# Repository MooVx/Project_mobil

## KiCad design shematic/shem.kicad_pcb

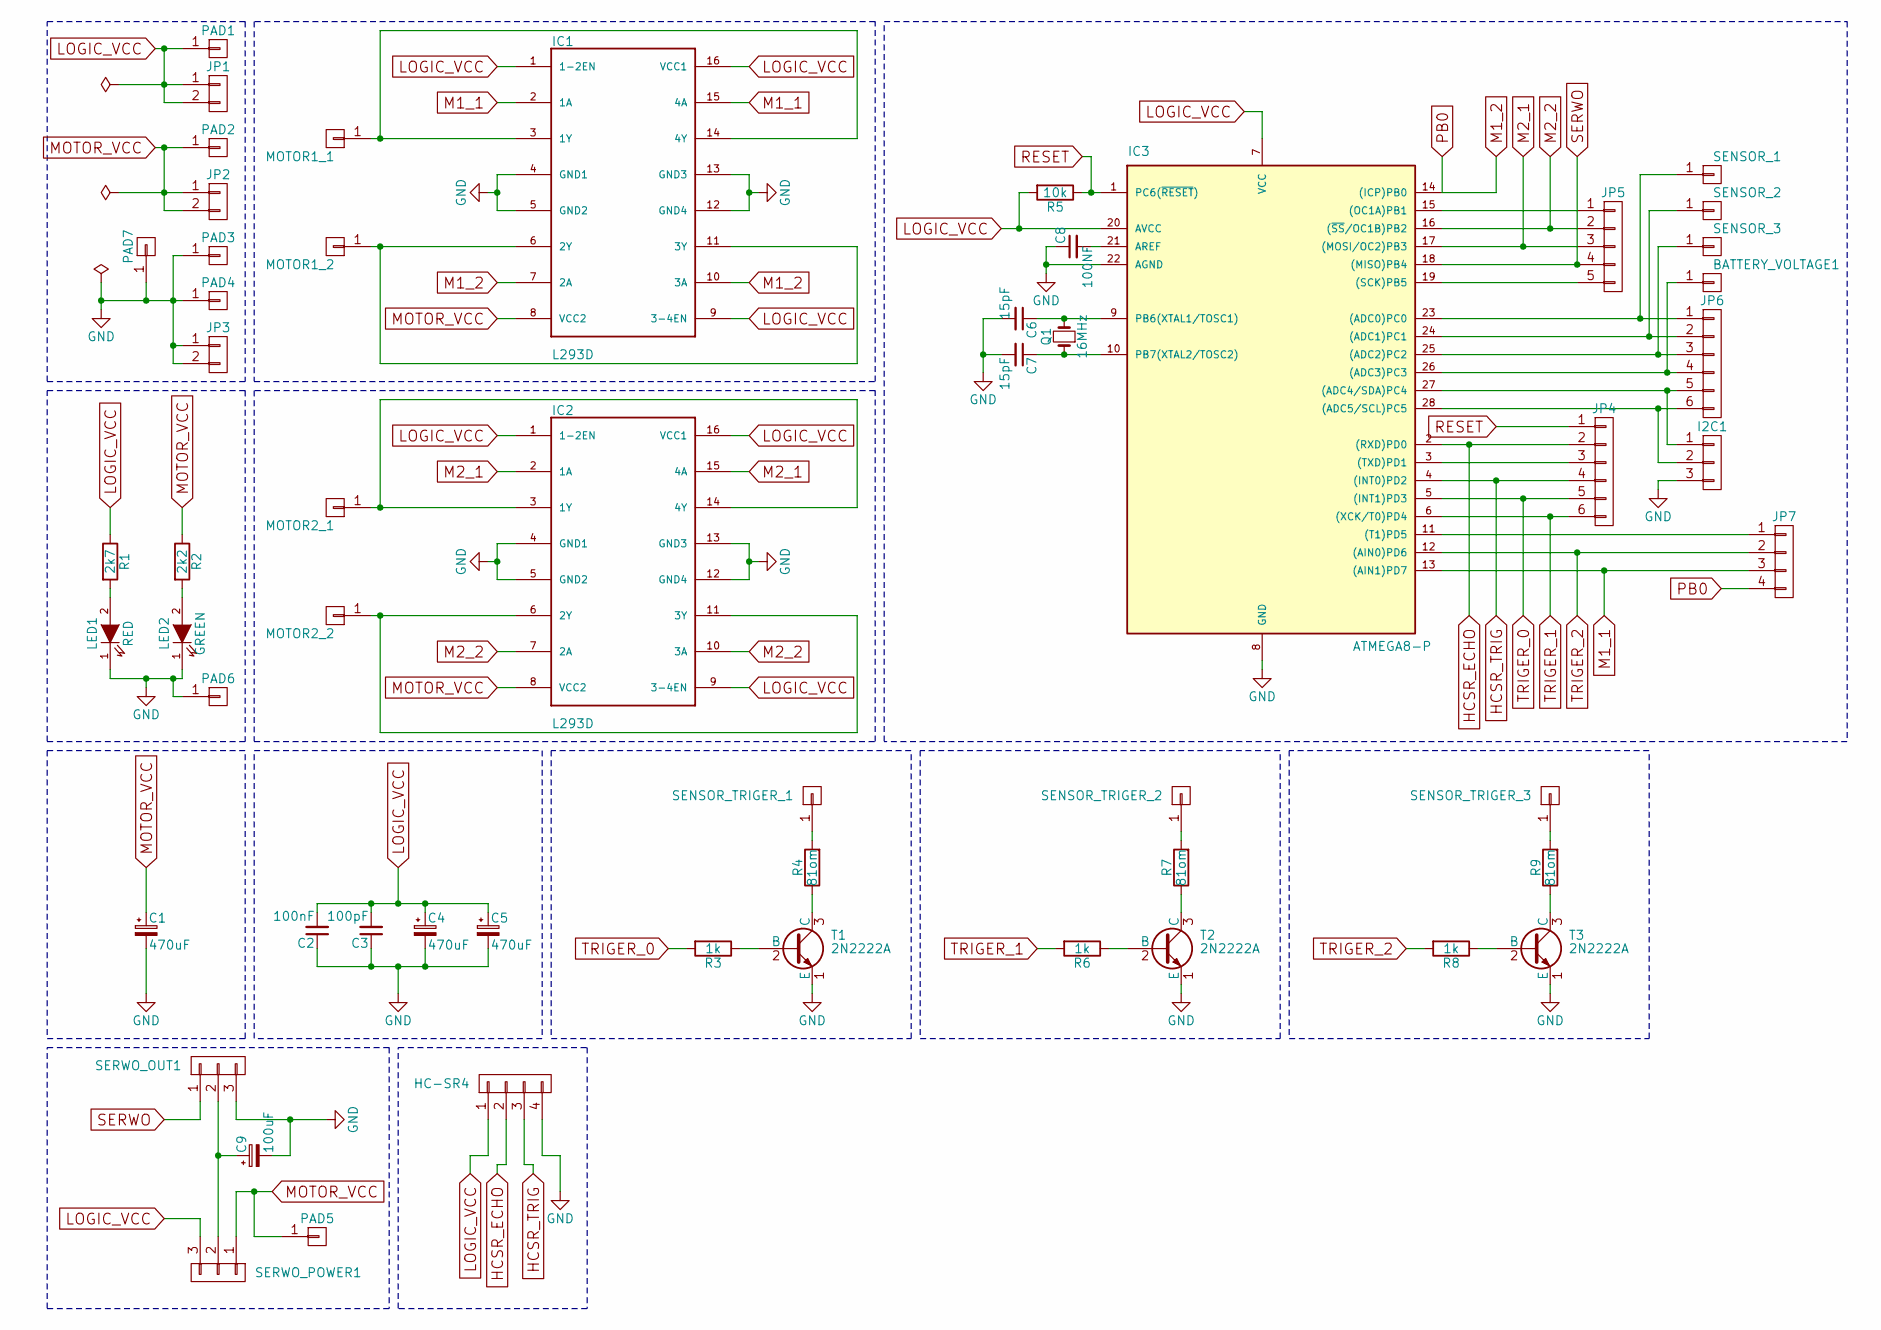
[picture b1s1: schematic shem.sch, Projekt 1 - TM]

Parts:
BATTERY_VOLTAGE1: CONN_01X01; SolderWirePad_single_1-5mmDrill
C1, C4, C5: 470uF; CP_Radial_D8.0mm_P3.80mm
C2: 100nF; C_Rect_L7.0mm_W2.0mm_P5.00mm
C3: 100pF; C_Disc_D3.8mm_W2.6mm_P2.50mm
C6, C7: 15pF; C_Disc_D3.4mm_W2.1mm_P2.50mm
C8: 100NF; C_Disc_D5.0mm_W2.5mm_P2.50mm
C9: 100uF; CP_Radial_D5.0mm_P2.00mm
HC-SR4: CONN_01X04; Pin_Header_Straight_1x04_Pitch2.54mm
I2C1: CONN_01X03; Pin_Header_Straight_1x03_Pitch2.54mm
IC1, IC2: L293D; DIP-16_W7.62mm_LongPads
IC3: ATMEGA8-P; DIP-28_W7.62mm_LongPads
JP1, JP2, JP3: CONN_01X02; Pin_Header_Straight_1x02_Pitch2.54mm
JP4, JP6: CONN_01X06; Pin_Header_Straight_1x06_Pitch2.54mm
JP5: CONN_01X05; Pin_Header_Straight_1x05_Pitch2.54mm
JP7: CONN_01X04; Pin_Header_Straight_1x04_Pitch2.54mm
LED1: RED; LED_D5.0mm
LED2: GREEN; LED_D5.0mm
MOTOR1_1, MOTOR1_2, MOTOR2_1, MOTOR2_2: CONN_01X01; SolderWirePad_single_1-5mmDrill
PAD1, PAD2, PAD3, PAD4, PAD5, PAD6, PAD7: CONN_01X01; SolderWirePad_single_1-2mmDrill
Q1: 16MHz; Crystal_HC49-U_Vertical
R1: 2k7; R_Axial_DIN0207_L6.3mm_D2.5mm_P10.16mm_Horizontal
R2: 2k2; R_Axial_DIN0207_L6.3mm_D2.5mm_P10.16mm_Horizontal
R3, R6, R8: 1k; R_Axial_DIN0207_L6.3mm_D2.5mm_P10.16mm_Horizontal
R4, R7, R9: 81om; R_Axial_DIN0207_L6.3mm_D2.5mm_P10.16mm_Horizontal
R5: 10k; R_Axial_DIN0207_L6.3mm_D2.5mm_P10.16mm_Horizontal
SENSOR_1, SENSOR_2, SENSOR_3: CONN_01X01; SolderWirePad_single_1-5mmDrill
SENSOR_TRIGER_1, SENSOR_TRIGER_2, SENSOR_TRIGER_3: CONN_01X01; SolderWirePad_single_1-5mmDrill
SERWO_OUT1: CONN_01X03; Pin_Header_Straight_1x03_Pitch2.54mm
SERWO_POWER1: CONN_01X03; Pin_Header_Straight_1x03_Pitch2.54mm
T1, T2, T3: 2N2222A; TO-92_Molded_Narrow

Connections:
GND: C1.2, C2.1, C3.1, C4.2, C5.2, C6.2, C7.2, C8.1, C9.2, HC-SR4.4, I2C1.3, IC1.4 (GND1), IC1.5 (GND2), IC1.12 (GND4), IC1.13 (GND3), IC2.4 (GND1), IC2.5 (GND2), IC2.12 (GND4), IC2.13 (GND3), IC3.8 (GND), IC3.22 (AGND), JP3.1, JP3.2, LED1.1 (K), LED2.1 (K), PAD3.1, PAD4.1, PAD6.1, PAD7.1, SERWO_OUT1.3, T1.1 (E), T2.1 (E), T3.1 (E); also elsewhere on the board
HCSR_ECHO: HC-SR4.2, IC3.2 ((RXD)PD0), JP4.2
HCSR_TRIG: HC-SR4.3, IC3.4 ((INT0)PD2), JP4.4
LOGIC_VCC: C2.2, C3.2, C4.1, C5.1, HC-SR4.1, IC1.1 (1-2EN), IC1.9 (3-4EN), IC1.16 (VCC1), IC2.1 (1-2EN), IC2.9 (3-4EN), IC2.16 (VCC1), IC3.7 (VCC), IC3.20 (AVCC), JP1.1, JP1.2, PAD1.1, R1.1, R5.2, SERWO_POWER1.3; also elsewhere on the board
M1_1: IC1.2 (1A), IC1.15 (4A), IC3.13 ((AIN1)PD7), JP7.3
M1_2: IC1.7 (2A), IC1.10 (3A), IC3.14 ((ICP)PB0), JP7.4
M2_1: IC2.2 (1A), IC2.15 (4A), IC3.17 ((MOSI/OC2)PB3), JP5.3
M2_2: IC2.7 (2A), IC2.10 (3A), IC3.16 ((~SS~/OC1B)PB2), JP5.2
MOTOR_VCC: C1.1, IC1.8 (VCC2), IC2.8 (VCC2), JP2.1, JP2.2, PAD2.1, PAD5.1, R2.1, SERWO_POWER1.1; also elsewhere on the board
unnamed 9: BATTERY_VOLTAGE1.1, IC3.26 ((ADC3)PC3), JP6.4; also elsewhere on the board
unnamed: C6.1, IC3.9 (PB6(XTAL1/TOSC1)), Q1.2
unnamed: C7.1, IC3.10 (PB7(XTAL2/TOSC2)), Q1.1
unnamed: C8.2, IC3.21 (AREF)
unnamed 13: C9.1, SERWO_OUT1.2, SERWO_POWER1.2; also elsewhere on the board
unnamed 14: I2C1.1, IC3.27 ((ADC4/SDA)PC4), JP6.5; also elsewhere on the board
unnamed 15: I2C1.2, IC3.28 ((ADC5/SCL)PC5), JP6.6; also elsewhere on the board
unnamed: IC1.6 (2Y), IC1.11 (3Y), MOTOR1_2.1
unnamed: IC1.3 (1Y), IC1.14 (4Y), MOTOR1_1.1
unnamed: IC2.6 (2Y), IC2.11 (3Y), MOTOR2_2.1
unnamed: IC2.3 (1Y), IC2.14 (4Y), MOTOR2_1.1
unnamed: IC3.3 ((TXD)PD1), JP4.3
unnamed: IC3.11 ((T1)PD5), JP7.1
unnamed: IC3.15 ((OC1A)PB1), JP5.1
unnamed: IC3.19 ((SCK)PB5), JP5.5
unnamed: IC3.23 ((ADC0)PC0), JP6.1, SENSOR_1.1
unnamed: IC3.24 ((ADC1)PC1), JP6.2, SENSOR_2.1
unnamed: IC3.25 ((ADC2)PC2), JP6.3, SENSOR_3.1
unnamed: LED1.2 (A), R1.2
unnamed: LED2.2 (A), R2.2
unnamed: R3.1, T1.2 (B)
unnamed: R4.1, T1.3 (C)
unnamed: R4.2, SENSOR_TRIGER_1.1
unnamed: R6.1, T2.2 (B)
unnamed: R7.1, T2.3 (C)
unnamed: R7.2, SENSOR_TRIGER_2.1
unnamed: R8.1, T3.2 (B)
unnamed: R9.1, T3.3 (C)
unnamed: R9.2, SENSOR_TRIGER_3.1
RESET: IC3.1 (PC6(~RESET~)), JP4.1, R5.1
SERWO: IC3.18 ((MISO)PB4), JP5.4, SERWO_OUT1.1; also elsewhere on the board
TRIGER_0: IC3.5 ((INT1)PD3), JP4.5, R3.2
TRIGER_1: IC3.6 ((XCK/T0)PD4), JP4.6, R6.2
TRIGER_2: IC3.12 ((AIN0)PD6), JP7.2, R8.2

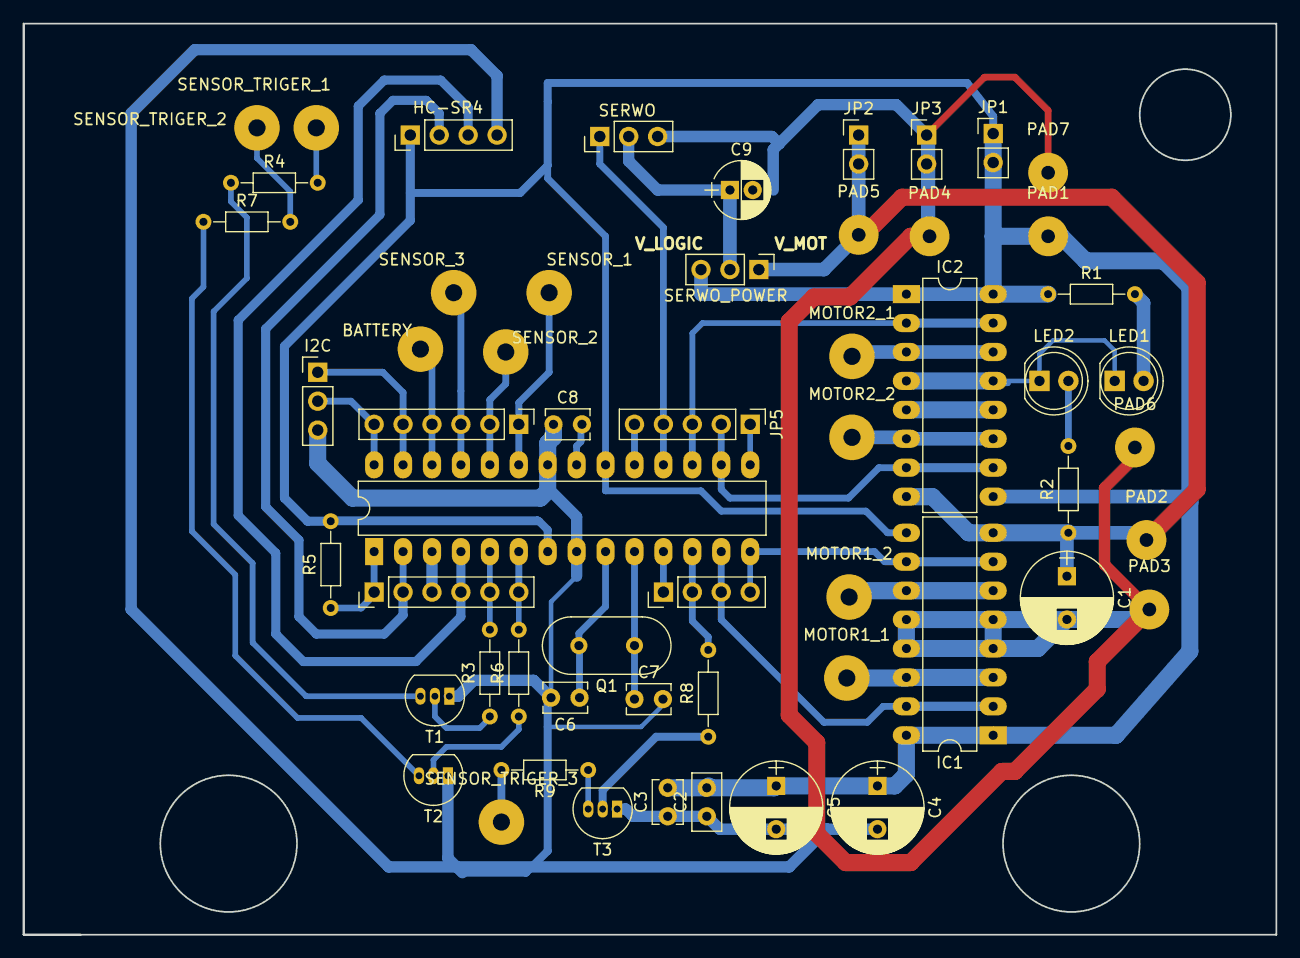
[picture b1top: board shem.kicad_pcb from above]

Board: 2 copper layers, 110.0 x 80.0 mm, 56 parts (0 on the bottom side), 43 nets.

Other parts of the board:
BATTERY: CONN_01X01; SolderWirePad_single_1-5mmDrill
I2C: CONN_01X03; Pin_Header_Straight_1x03_Pitch2.54mm
SERWO: CONN_01X03; Pin_Header_Straight_1x03_Pitch2.54mm
SERWO_POWER: CONN_01X03; Pin_Header_Straight_1x03_Pitch2.54mm

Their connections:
GND: I2C.3, SERWO.3; also elsewhere on the board
LOGIC_VCC: SERWO_POWER.3; also elsewhere on the board
MOTOR_VCC: SERWO_POWER.1; also elsewhere on the board
unnamed 9: BATTERY.1; also elsewhere on the board
unnamed 13: SERWO.2, SERWO_POWER.2; also elsewhere on the board
unnamed 14: I2C.1; also elsewhere on the board
unnamed 15: I2C.2; also elsewhere on the board
SERWO: SERWO.1; also elsewhere on the board

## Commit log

2017-03-21 test
2017-03-21 shem
2017-03-23 added some outputs
2017-03-23 board start
2017-03-25 pcb shem finish
2017-03-25 Zdjecia do dokumentacji
    Schematy poszczegolnych sekcji + PDF zawierajacy caly schemat.
2017-03-25 Updata
    Wykonana plytka
2017-03-25 Sprawko + dokumentacja
    Gotowe do wyslania ;-)
2017-04-05 Sprawko - Etap2
2017-04-27 spr3
